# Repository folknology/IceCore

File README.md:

# IceCore
IceCore Ice40 HX based modular developement core 

**Top View**

**Bottom View**

**Features**
* Ice40 HX4K - 4K Luts (8K for Yosys), 80/(128)Kbits BRAM, 2 PLLs, NVCM
* 16Mbit SDRAM 16 bits wide (143Mhz)
* 4Mbit Flash QSPI/SPI (100Mhz)
* 56 General purpose IOs, SPI, Uart, I2C/Can
* Stm32F730 200Mhz, 256KB Ram, 64KB Flash
* Triple 2.5MSPS ADCs (interleaved to 7.2MSPS)
* Dedicated Programming and debug USB 2.0FS
* Uart/Application specific USB2.0FS
* Digital video connector
* SDCard connector
* 4 Coloured Status LEDs
* 4 Coloured User LEDs
* 2 User buttons, 1 Mode/Boot buttoni

[Get it from Tindie as part of BlackIce Mx](https://www.tindie.com/products/Folknology/blackice-mx/)

Core modules can be combined with different carrier boards for example [BlackIce Mx](https://github.com/folknology/BlackIceMx)

Supports the [BlackEdge connectivity](https://github.com/folknology/BlackEdge) carriers

Some further [background information](https://forum.mystorm.uk/t/new-product-blackice-mx/551/10) can be found on the [myStorm forum](https://forum.mystorm.uk)

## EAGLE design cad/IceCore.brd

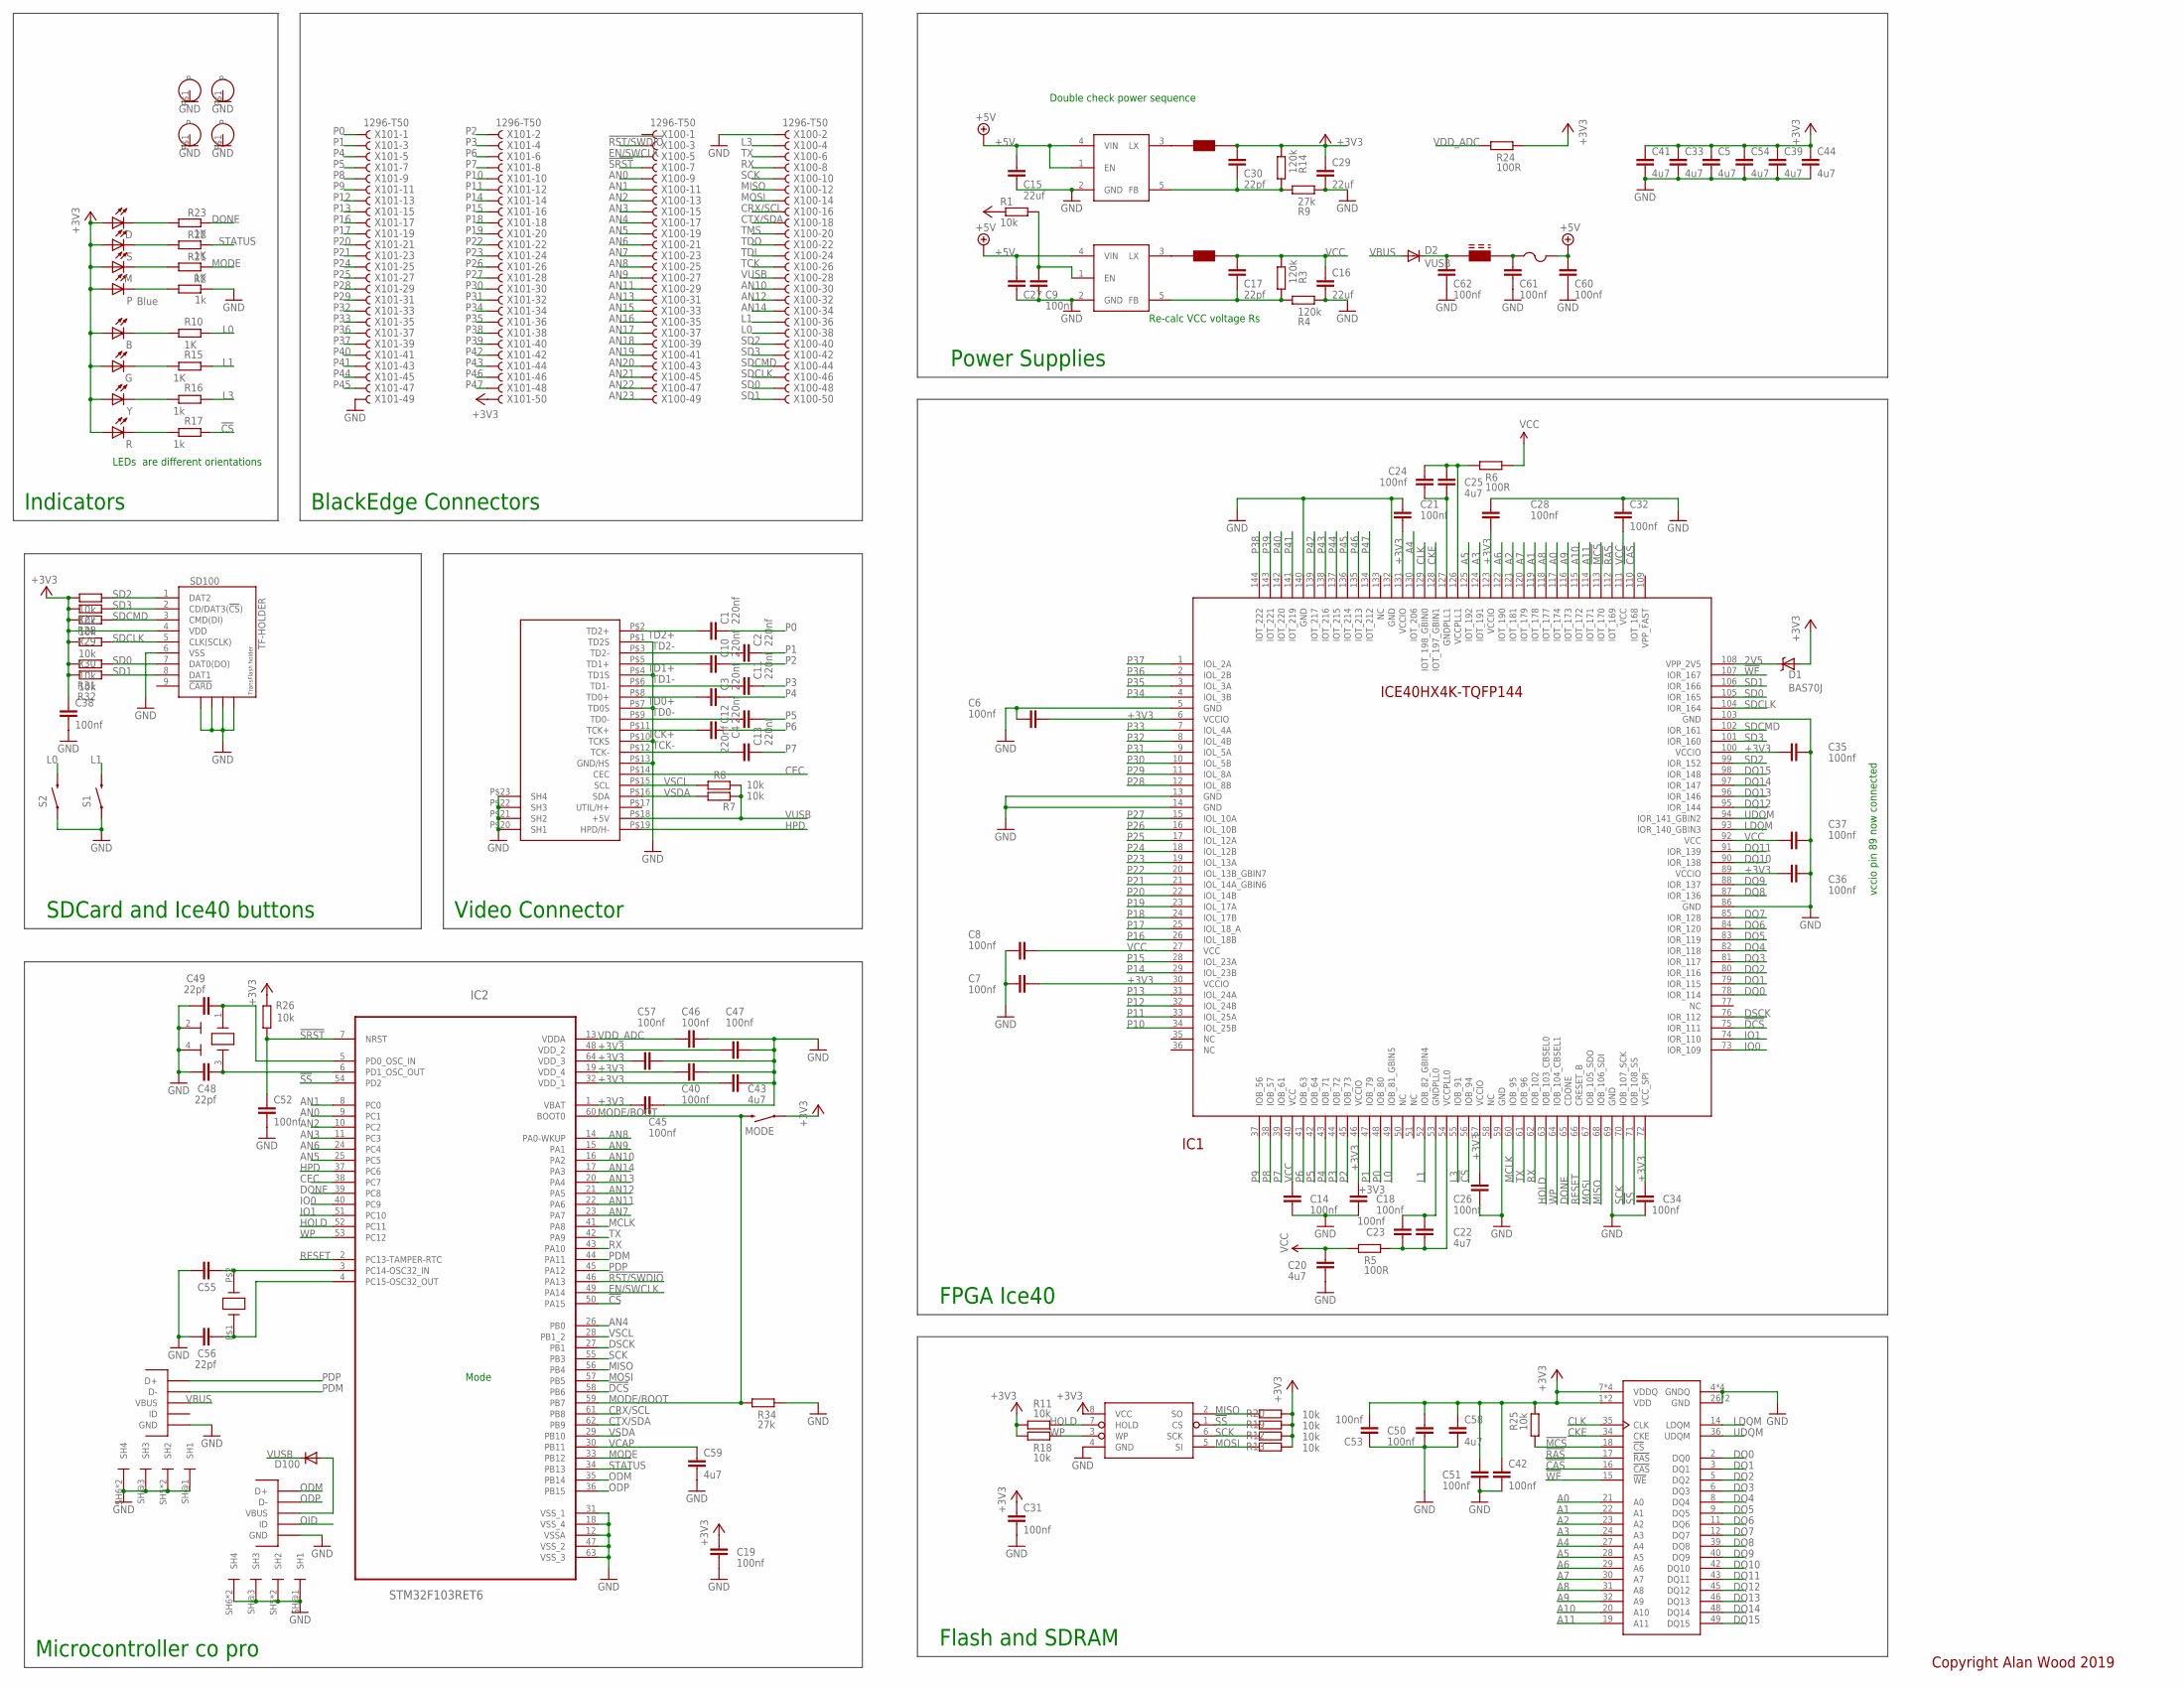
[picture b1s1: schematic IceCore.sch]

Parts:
B: LEDCHIPLED_0603; CHIPLED_0603
C1, C2, C3, C4, C10, C11, C12, C13: 220nf; C0402
C5, C20, C22, C25, C33, C39, C41, C43, C44, C54, C58, C59: 4u7; C0402
C6, C7, C8, C9, C14, C18, C19, C21, C23, C24, C26, C28, C31, C32, C34, C35, C36, C37, C38, C40, C42, C45, C46, C47, C50, C51, C52, C53, C57, C60, C61, C62: 100nf; C0402
C15, C16, C27, C29: 22uf; C0603
C17, C30, C48, C49, C55, C56: 22pf; C0402
COM: FCI-MICROUSB-B-PEG; MICROUSB-B-PEG
D: LEDCHIPLED_0603; CHIPLED_0603
D1: BAS70J; SOD-323
D2, D100: DIODE-SOD123; SOD123
F1: PTCFUSE-1206; R1206
FB1: FERRITE_BEAD; 0603
G: LEDCHIPLED_0603; CHIPLED_0603
IC1: ICE40HX4K_TQFP144; TQFP144
IC2: STM32F103RET6; QFP50P1200X1200X160-64N
IC3: SDRAM; TSOP-2-50
M: LEDCHIPLED_0603; CHIPLED_0603
MODE: SWITCH-MOMENTARY-2SMD-1101NE; TACTILE-SWITCH-1101NE
P: Blue; CHIPLED_0603
R: LEDCHIPLED_0603; CHIPLED_0603
R1, R7, R8, R11, R12, R13, R18, R19, R20, R25, R26, R27, R28, R29, R30, R31, R32: 10k; R0402
R2, R16, R17: 1k; R0402
R3, R4, R14: 120k; R0402
R5, R6, R24: 100R; R0402
R9, R34: 27k; R0402
R10, R15, R21, R22, R23: 1K; R0402
S: LEDCHIPLED_0603; CHIPLED_0603
S1, S2: SWITCH-MOMENTARY-2SMD-1101NE; TACTILE-SWITCH-1101NE
SD100: TF-HOLDER; TF-PULL
U$1, U$2, U$12, U$13: HOLE-2.5MM; 2.5MM-HOLE
U$3, U$6: AP3429/A; TSOP-5/SOT23-5
U$4, U$7: NRS4018; NRC4018
U$5: HD10-001_HDMIMINI-HDMI; MINI-HDMI
U$8: AT25SDF041A; SOIC-8-NARROW
U$10: FCI-MICROUSB-B-PEG; MICROUSB-B-PEG
U$11: FC-135; FC135
X100, X101: 1296-T50; 1296-50
Y: LEDCHIPLED_0603; CHIPLED_0603
Y1: 12MZ; CRYSTAL-3.2X2.5

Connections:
2V5: D1.C, IC1.108 (VPP_2V5)
!CAS: IC1.110 (IOT_168), IC3.16 (!CAS)
!CS: IC1.56 (IOB_94), IC2.50 (PA15), R17.2
!DCS: IC1.75 (IOR_111), IC2.58 (PB6)
!MCS: IC1.113 (IOT_170), IC3.18 (!CS), R25.1
!RAS: IC1.112 (IOT_169), IC3.17 (!RAS)
!RST/SWDIO: IC2.46 (PA13), X100.3
!SRST: C52.1, IC2.7 (NRST), R26.1, X100.7
!SS: IC1.71 (IOB_108_SS), IC2.54 (PD2), R19.2, U$8.1 (CS)
!WE: IC1.107 (IOR_167), IC3.15 (!WE)
+3V3: B.A, C5.1, C6.1, C7.2, C18.1, C19.1, C21.1, C26.1, C28.2, C29.1, C30.2, C31.1, C33.1, C34.1, C35.1, C36.1, C38.1, C39.1, C40.2, C41.1, C42.1, C43.2, C44.1, C45.2, C47.2, C50.1, C51.1, C53.2, C54.1, C57.2, C58.1, D.A, D1.A, G.A, IC1.6 (VCCIO), IC1.30 (VCCIO), IC1.46 (VCCIO), IC1.57 (VCCIO), IC1.72 (VCC_SPI), IC1.89 (VCCIO), IC1.100 (VCCIO), IC1.123 (VCCIO), IC1.131 (VCCIO), IC2.1 (VBAT), IC2.19 (VDD_4), IC2.32 (VDD_1), IC2.48 (VDD_2), IC2.64 (VDD_3), IC3.1 (VDD), IC3.7 (VDDQ), IC3.13 (VDDQ), IC3.25 (VDD), IC3.38 (VDDQ), IC3.44 (VDDQ), M.A, MODE.1, P.A, R.A, R1.1, R11.1, R12.1, R13.1, R14.2, R18.1, R19.1, R20.1, R24.1, R25.2, R26.2, R27.2, R28.2, R29.2, R30.2, R31.2, R32.2, S.A, SD100.4 (VDD), U$7.P$2, U$8.8 (VCC), X101.50, Y.A
+5V: C15.2, C27.2, C60.2, F1.2, U$3.4 (VIN), U$6.1 (EN), U$6.4 (VIN)
A0: IC1.117 (IOT_174), IC3.21 (A0)
A1: IC1.119 (IOT_178), IC3.22 (A1)
A2: IC1.121 (IOT_181), IC3.23 (A2)
A3: IC1.124 (IOT_191), IC3.24 (A3)
A4: IC1.130 (IOT_206), IC3.27 (A4)
A5: IC1.125 (IOT_192), IC3.28 (A5)
A6: IC1.122 (IOT_190), IC3.29 (A6)
A7: IC1.120 (IOT_179), IC3.30 (A7)
A8: IC1.118 (IOT_177), IC3.31 (A8)
A9: IC1.116 (IOT_173), IC3.32 (A9)
A10: IC1.115 (IOT_172), IC3.20 (A10)
A11: IC1.114 (IOT_171), IC3.19 (A11)
AN0: IC2.9 (PC1), X100.9
AN1: IC2.8 (PC0), X100.11
AN2: IC2.10 (PC2), X100.13
AN3: IC2.11 (PC3), X100.15
AN4: IC2.26 (PB0), X100.17
AN5: IC2.25 (PC5), X100.19
AN6: IC2.24 (PC4), X100.21
AN7: IC2.23 (PA7), X100.23
AN8: IC2.14 (PA0-WKUP), X100.25
AN9: IC2.15 (PA1), X100.27
AN10: IC2.16 (PA2), X100.30
AN11: IC2.22 (PA6), X100.29
AN12: IC2.21 (PA5), X100.32
AN13: IC2.20 (PA4), X100.31
AN14: IC2.17 (PA3), X100.34
AN15: X100.33
AN16: X100.35
AN17: X100.37
AN18: X100.39
AN19: X100.41
AN20: X100.43
AN21: X100.45
AN22: X100.47
AN23: X100.49
CEC: IC2.38 (PC7), U$5.P$14 (CEC)
CKE: IC1.128 (IOT_197_GBIN1), IC3.34 (CKE)
CLK: IC1.129 (IOT_198_GBIN0), IC3.35 (CLK)
CRX/SCL: IC2.61 (PB8), X100.16
CTX/SDA: IC2.62 (PB9), X100.18
DONE: IC1.65 (CDONE), IC2.39 (PC8), R23.1
DQ0: IC1.78 (IOR_114), IC3.2 (DQ0)
DQ1: IC1.79 (IOR_115), IC3.3 (DQ1)
DQ2: IC1.80 (IOR_116), IC3.5 (DQ2)
DQ3: IC1.81 (IOR_117), IC3.6 (DQ3)
DQ4: IC1.82 (IOR_118), IC3.8 (DQ4)
DQ5: IC1.83 (IOR_119), IC3.9 (DQ5)
DQ6: IC1.84 (IOR_120), IC3.11 (DQ6)
DQ7: IC1.85 (IOR_128), IC3.12 (DQ7)
DQ8: IC1.87 (IOR_136), IC3.39 (DQ8)
DQ9: IC1.88 (IOR_137), IC3.40 (DQ9)
DQ10: IC1.90 (IOR_138), IC3.42 (DQ10)
DQ11: IC1.91 (IOR_139), IC3.43 (DQ11)
DQ12: IC1.95 (IOR_144), IC3.45 (DQ12)
DQ13: IC1.96 (IOR_146), IC3.46 (DQ13)
DQ14: IC1.97 (IOR_147), IC3.48 (DQ14)
DQ15: IC1.98 (IOR_148), IC3.49 (DQ15)
DSCK: IC1.76 (IOR_112), IC2.27 (PB1)
EN/SWCLK: IC2.49 (PA14), X100.5
GND: C5.2, C6.2, C7.1, C8.2, C9.1, C14.2, C15.1, C16.2, C18.2, C19.2, C20.2, C21.2, C26.2, C27.1, C28.1, C29.2, C31.2, C32.1, C33.2, C34.2, C35.2, C36.2, C37.2, C38.2, C39.2, C40.1, C41.2, C42.2, C43.1, C44.2, C45.1, C46.1, C47.1, C48.1, C49.1, C50.2, C51.2, C52.2, C53.1, C54.2, C55.1, C56.1, C57.1, C58.2, C59.2, C60.1, C61.1, C62.1, COM.P$5 (GND), COM.SH5 (SH2), COM.SH6 (SH4), COM.SH@1 (SH1), COM.SH@2 (SH2), COM.SH@3 (SH3), COM.SH@4 (SH4), IC1.5 (GND), IC1.13 (GND), IC1.14 (GND), IC1.59 (GND), IC1.69 (GND), IC1.86 (GND), IC1.103 (GND), IC1.132 (GND), IC1.140 (GND), IC2.12 (VSSA), IC2.18 (VSS_4), IC2.31 (VSS_1), IC2.47 (VSS_2), IC2.63 (VSS_3), IC3.4 (GNDQ), IC3.10 (GNDQ), IC3.26 (GND), IC3.41 (GNDQ), IC3.47 (GNDQ), IC3.50 (GND), R2.1, R4.2, R9.2, R34.2, S1.1, S2.1, SD100.6 (VSS), SD100.S1, SD100.S2, SD100.S3, SD100.S4, U$1.P$1, U$2.P$1, U$3.2 (GND), U$5.P$1 (TD2S), U$5.P$4 (TD1S), U$5.P$7 (TD0S), U$5.P$10 (TCKS), U$5.P$13 (GND/HS), U$5.P$20 (SH1), U$5.P$21 (SH2), U$5.P$22 (SH3), U$5.P$23 (SH4), U$6.2 (GND), U$8.4 (GND), U$10.P$5 (GND), U$10.SH5 (SH2), U$10.SH6 (SH4), U$10.SH@1 (SH1), U$10.SH@2 (SH2), U$10.SH@3 (SH3), U$10.SH@4 (SH4), U$12.P$1, U$13.P$1, X100.2, X101.49, Y1.2 (GND), Y1.4 (GND)
HOLD: IC1.63 (IOB_103_CBSEL0), IC2.52 (PC11), R11.2, U$8.7 (HOLD)
HPD: IC2.37 (PC6), U$5.P$19 (HPD/H-)
IO0: IC1.73 (IOR_109), IC2.40 (PC9)
IO1: IC1.74 (IOR_110), IC2.51 (PC10)
L0: IC1.49 (IOB_81_GBIN5), R10.2, S2.2, X100.38
L1: IC1.52 (IOB_82_GBIN4), R15.2, S1.2, X100.36
L3: IC1.55 (IOB_91), R16.2, X100.4
LDQM: IC1.93 (IOR_140_GBIN3), IC3.14 (LDQM)
MCLK: IC1.60 (IOB_95), IC2.41 (PA8)
MISO: IC1.68 (IOB_106_SDI), IC2.56 (PB4), R20.2, U$8.2 (SO), X100.12
MODE: IC2.33 (PB12), R21.1
MODE/BOOT: IC2.59 (PB7), IC2.60 (BOOT0), MODE.2, R34.1
MOSI: IC1.67 (IOB_105_SDO), IC2.57 (PB5), R13.2, U$8.5 (SI), X100.14
unnamed: P.C, R2.2
unnamed: R22.2, S.C
unnamed: C24.2, C25.2, IC1.126 (VCCPLL1), R6.2
unnamed: M.C, R21.2
unnamed: C56.2, IC2.4 (PC15-OSC32_OUT), U$11.P$1 (X1)
unnamed: C22.1, C23.2, IC1.53 (GNDPLL0)
unnamed: C48.2, IC2.6 (PD1_OSC_OUT), Y1.3 (X2)
unnamed: C9.2, R1.2, U$3.1 (EN)
unnamed: B.C, R10.1
unnamed: C55.2, IC2.3 (PC14-OSC32_IN), U$11.P$2 (X2)
unnamed: G.C, R15.1
unnamed: R16.1, Y.C
unnamed: COM.P$1 (VBUS), D100.A
unnamed: C24.1, C25.1, IC1.127 (GNDPLL1)
unnamed: R.C, R17.1
unnamed: C61.2, F1.1, FB1.2
unnamed: C22.2, C23.1, IC1.54 (VCCPLL0), R5.1
unnamed: C49.2, IC2.5 (PD0_OSC_IN), Y1.1 (X1)
unnamed: D.C, R23.2
unnamed: U$3.3 (LX), U$4.P$1
unnamed: C17.1, R3.1, R4.1, U$3.5 (FB)
unnamed: C30.1, R9.1, R14.1, U$6.5 (FB)
unnamed: U$6.3 (LX), U$7.P$1
ODM: COM.P$3 (D+), IC2.35 (PB14)
ODP: COM.P$2 (D-), IC2.36 (PB15)
OID: COM.P$4 (ID)
P0: C1.1, IC1.48 (IOB_80), X101.1
P1: C2.1, IC1.47 (IOB_79), X101.3
P2: C10.1, IC1.45 (IOB_73), X101.2
P3: C11.1, IC1.44 (IOB_72), X101.4
P4: C3.1, IC1.43 (IOB_71), X101.5
P5: C4.2, IC1.42 (IOB_64), X101.7
P6: C12.1, IC1.41 (IOB_63), X101.6
P7: C13.1, IC1.39 (IOB_61), X101.8
P8: IC1.38 (IOB_57), X101.9
P9: IC1.37 (IOB_56), X101.11
P10: IC1.34 (IOL_25B), X101.10
P11: IC1.33 (IOL_25A), X101.12
P12: IC1.32 (IOL_24B), X101.13
P13: IC1.31 (IOL_24A), X101.15
P14: IC1.29 (IOL_23B), X101.14
P15: IC1.28 (IOL_23A), X101.16
P16: IC1.26 (IOL_18B), X101.17
P17: IC1.25 (IOL_18_A), X101.19
P18: IC1.24 (IOL_17B), X101.18
P19: IC1.23 (IOL_17A), X101.20
P20: IC1.22 (IOL_14B), X101.21
P21: IC1.21 (IOL_14A_GBIN6), X101.23
P22: IC1.20 (IOL_13B_GBIN7), X101.22
P23: IC1.19 (IOL_13A), X101.24
P24: IC1.18 (IOL_12B), X101.25
P25: IC1.17 (IOL_12A), X101.27
P26: IC1.16 (IOL_10B), X101.26
P27: IC1.15 (IOL_10A), X101.28
P28: IC1.12 (IOL_8B), X101.29
P29: IC1.11 (IOL_8A), X101.31
P30: IC1.10 (IOL_5B), X101.30
P31: IC1.9 (IOL_5A), X101.32
P32: IC1.8 (IOL_4B), X101.33
P33: IC1.7 (IOL_4A), X101.35
P34: IC1.4 (IOL_3B), X101.34
P35: IC1.3 (IOL_3A), X101.36
P36: IC1.2 (IOL_2B), X101.37
P37: IC1.1 (IOL_2A), X101.39
P38: IC1.144 (IOT_222), X101.38
P39: IC1.143 (IOT_221), X101.40
P40: IC1.142 (IOT_220), X101.41
P41: IC1.141 (IOT_219), X101.43
P42: IC1.139 (IOT_217), X101.42
P43: IC1.138 (IOT_216), X101.44
P44: IC1.137 (IOT_215), X101.45
P45: IC1.136 (IOT_214), X101.47
P46: IC1.135 (IOT_213), X101.46
P47: IC1.134 (IOT_212), X101.48
PDM: IC2.44 (PA11), U$10.P$2 (D-)
PDP: IC2.45 (PA12), U$10.P$3 (D+)
RESET: IC1.66 (CRESET_B), IC2.2 (PC13-TAMPER-RTC)
RX: IC1.62 (IOB_102), IC2.43 (PA10), X100.8
SCK: IC1.70 (IOB_107_SCK), IC2.55 (PB3), R12.2, U$8.6 (SCK), X100.10
SD0: IC1.105 (IOR_165), R31.1, SD100.7 (DAT0(DO)), X100.48
SD1: IC1.106 (IOR_166), R32.1, SD100.8 (DAT1), X100.50
SD2: IC1.99 (IOR_152), R27.1, SD100.1 (DAT2), X100.40
SD3: IC1.101 (IOR_160), R28.1, SD100.2 (CD/DAT3(!CS!)), X100.42
SDCLK: IC1.104 (IOR_164), R30.1, SD100.5 (CLK(SCLK)), X100.46
SDCMD: IC1.102 (IOR_161), R29.1, SD100.3 (CMD(DI)), X100.44
STATUS: IC2.34 (PB13), R22.1
TCK: X100.26
TCK+: C12.2, U$5.P$11 (TCK+)
TCK-: C13.2, U$5.P$12 (TCK-)
TD0+: C3.2, U$5.P$8 (TD0+)
TD0-: C4.1, U$5.P$9 (TD0-)
TD1+: C10.2, U$5.P$5 (TD1+)
TD1-: C11.2, U$5.P$6 (TD1-)
TD2+: C1.2, U$5.P$2 (TD2+)
TD2-: C2.2, U$5.P$3 (TD2-)
TDI: X100.24
TDO: X100.22
TMS: X100.20
TX: IC1.61 (IOB_96), IC2.42 (PA9), X100.6
UDQM: IC1.94 (IOR_141_GBIN2), IC3.36 (UDQM)
VBUS: D2.A, U$10.P$1 (VBUS)
VCAP: C59.1, IC2.30 (PB11)
VCC: C8.1, C14.1, C16.1, C17.2, C20.1, C32.2, C37.1, IC1.27 (VCC), IC1.40 (VCC), IC1.92 (VCC), IC1.111 (VCC), R3.2, R5.2, R6.1, U$4.P$2
VDD_ADC: C46.2, IC2.13 (VDDA), R24.2
VSCL: IC2.28 (PB1_2), R8.2, U$5.P$15 (SCL)
VSDA: IC2.29 (PB10), R7.2, U$5.P$16 (SDA)
VUSB: C62.2, D2.C, D100.C, FB1.1, R7.1, R8.1, U$5.P$18 (+5V), X100.28
WP: IC1.64 (IOB_104_CBSEL1), IC2.53 (PC12), R18.2, U$8.3 (WP)

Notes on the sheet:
BlackEdge Connectors
Video Connector
FPGA Ice40
Flash and SDRAM
Microcontroller co pro
SDCard and Ice40 buttons
vccio pin 89 now connected
Re-calc VCC voltage Rs
Indicators
Power Supplies
Double check power sequence
LEDs are different orientations
Mode
Copyright Alan Wood 2019

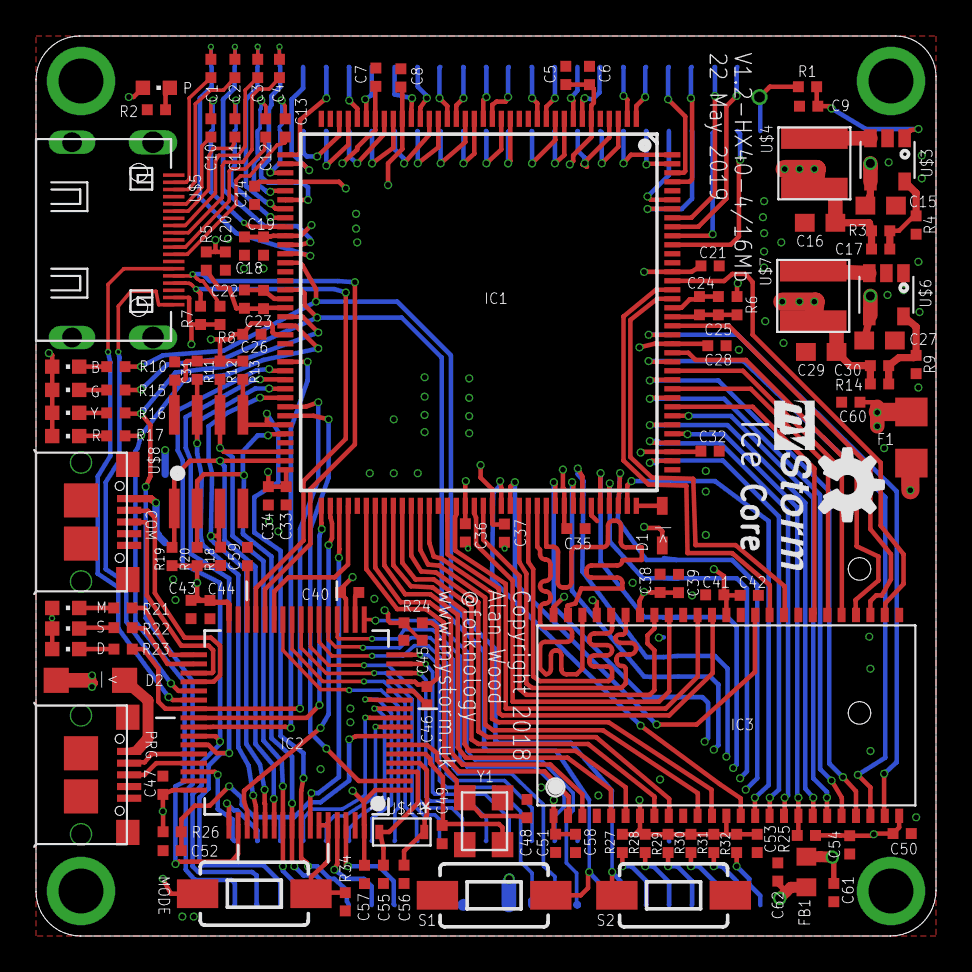
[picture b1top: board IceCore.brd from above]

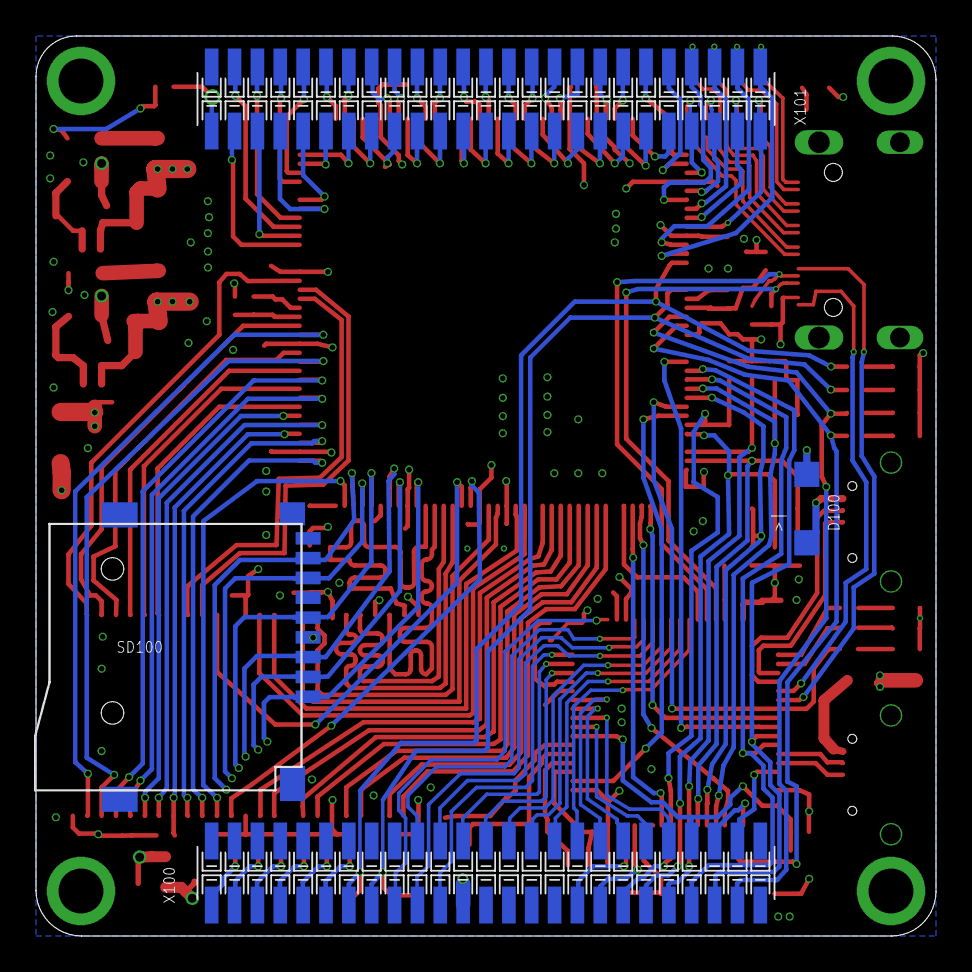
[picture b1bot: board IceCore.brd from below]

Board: 4 copper layers, 50.0 x 50.0 mm, 131 parts (4 on the bottom side), 180 nets.

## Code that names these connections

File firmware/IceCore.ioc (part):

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Mcu.Name=STM32F730R8Tx
Mcu.Package=LQFP64
Mcu.UserName=STM32F730R8Tx
PA0-WKUP.Signal=ADCx_IN0
PA1.Signal=ADCx_IN1
PA10.Mode=Asynchronous
PA10.Signal=USART1_RX
PA11.Mode=Device_Only
PA11.Signal=USB_OTG_FS_DM
PA12.Mode=Device_Only
PA12.Signal=USB_OTG_FS_DP
PA13.Mode=Serial_Wire
PA13.Signal=SYS_JTMS-SWDIO
PA14.Mode=Serial_Wire
PA14.Signal=SYS_JTCK-SWCLK
PA15.Mode=NSS_Signal_Hard_Input
PA15.Signal=SPI3_NSS
PA2.Signal=ADCx_IN2
PA3.Signal=ADCx_IN3
PA4.Signal=ADCx_IN4
PA5.Signal=ADCx_IN5
PA6.Signal=ADCx_IN6
PA7.Signal=ADCx_IN7
PA8.Mode=Clock-out-1
PA8.Signal=RCC_MCO_1
PA9.Mode=Asynchronous
PA9.Signal=USART1_TX
PB0.Signal=ADCx_IN8
PB1.Signal=ADCx_IN9
PB10.Mode=I2C
PB10.Signal=I2C2_SCL
PB11.Mode=I2C
PB11.Signal=I2C2_SDA
PB12.GPIOParameters=GPIO_Label
PB12.GPIO_Label=MODE_LED
PB12.Signal=GPIO_Output
PB13.GPIOParameters=GPIO_Label
PB13.GPIO_Label=STATUS_LED
PB13.Signal=GPIO_Output
PB2.Mode=Single Bank 1 2IOs
PB2.Signal=QUADSPI_CLK
PB3.Mode=Full_Duplex_Slave
PB3.Signal=SPI3_SCK
PB4.Mode=Full_Duplex_Slave
PB4.Signal=SPI3_MISO
PB5.Mode=Full_Duplex_Slave
PB5.Signal=SPI3_MOSI
PB6.Mode=Single Bank 1 2IOs
PB6.Signal=QUADSPI_BK1_NCS
PB7.GPIOParameters=GPIO_Label
PB7.GPIO_Label=MODE_BOOT
PB7.Signal=GPIO_Input
PB8.Mode=I2C
PB8.Signal=I2C1_SCL
PB9.Mode=I2C
PB9.Signal=I2C1_SDA
PC0.Signal=ADCx_IN10
PC1.Signal=ADCx_IN11
PC10.Mode=Single Bank 1 2IOs
PC10.Signal=QUADSPI_BK1_IO1
PC11.GPIOParameters=GPIO_Label,GPIO_ModeDefaultOutputPP
PC11.GPIO_Label=ICE40_HOLD
PC11.GPIO_ModeDefaultOutputPP=GPIO_MODE_OUTPUT_OD
PC11.Signal=GPIO_Output
PC12.GPIOParameters=GPIO_Label,GPIO_ModeDefaultOutputPP
PC12.GPIO_Label=ICE40_WP
PC12.GPIO_ModeDefaultOutputPP=GPIO_MODE_OUTPUT_OD
PC12.Signal=GPIO_Output
PC13.GPIOParameters=GPIO_Label
PC13.GPIO_Label=ICE40_CRST
PC13.Signal=GPIO_Output
PC14-OSC32_IN.Mode=LSE-External-Oscillator
PC14-OSC32_IN.Signal=RCC_OSC32_IN
PC15-OSC32_OUT.Mode=LSE-External-Oscillator
PC15-OSC32_OUT.Signal=RCC_OSC32_OUT
PC2.Signal=ADCx_IN12
PC3.Signal=ADCx_IN13
PC4.Signal=ADCx_IN14
PC6.GPIOParameters=GPIO_PuPd,GPIO_Label
PC6.GPIO_Label=HDMI_HPD
PC6.GPIO_PuPd=GPIO_PULLDOWN
PC6.Signal=GPIO_Input
PC7.GPIOParameters=GPIO_Label
PC7.GPIO_Label=HDMI_CEC
PC7.Signal=GPIO_Output
PC8.GPIOParameters=GPIO_Label,GPIO_ModeDefaultEXTI
PC8.GPIO_Label=ICE40_CDONE
PC8.GPIO_ModeDefaultEXTI=GPIO_MODE_IT_RISING_FALLING
PC8.Signal=GPXTI8
PC9.Mode=Single Bank 1 2IOs
PC9.Signal=QUADSPI_BK1_IO0
PD2.GPIOParameters=GPIO_Label,GPIO_ModeDefaultOutputPP
PD2.GPIO_Label=ICE40_SPI_CS
PD2.GPIO_ModeDefaultOutputPP=GPIO_MODE_OUTPUT_OD
PD2.Signal=GPIO_Output
PH0-OSC_IN.Mode=HSE-External-Oscillator
PH0-OSC_IN.Signal=RCC_OSC_IN
PH1-OSC_OUT.Mode=HSE-External-Oscillator
PH1-OSC_OUT.Signal=RCC_OSC_OUT
RCC.HSE_VALUE=25000000
RCC.SYSCLKFreq_VALUE=216000000
RCC.SYSCLKSource=RCC_SYSCLKSOURCE_PLLCLK
board=custom

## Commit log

2019-05-18 Initial commit of IceCore cad
2019-05-18 Cropped proto image
2019-05-18 Cropped layout image
2019-05-18 Added solderpad hardware license
2019-05-18 Fixed typo in readme
2019-05-18 Added Schematic preview image
2019-05-18 Added Schematic preview image to readme
2019-05-18 Updated IceCore images
2019-05-18 Added IceCore Bottom of board shot
2019-05-18 Updated IceCore date information in CAD
2019-07-02 Added first BIMx Verilog example (trail)
2019-07-02 Added comprehensive PCF file for reference
2019-07-02 Added blink example
2019-07-02 Changed blink to red led rather than blue (also button!)
2019-07-03 Fixed led index, doh!
2019-07-03 Added stty -F /dev/ttyACM0 raw to make file upload target
2019-07-03 Updated IceCore JPEG to manufactured board
2019-07-03 Updated IceCore bottom JPEG to manufactured board
2019-07-03 Updated IceCore board
2019-07-03 Updated Readme - ref BlackEdge repo
2019-07-03 Added initial myStorm iceboot firmware
2019-07-03 Fix Yosys misspelling.
2019-07-03 Renamed clk to rclk (SDRAM clock) and stop it conflicting with 25mhz clk
2019-07-04 Added BSD License to iceboot
2019-07-04 Updated BSD License in iceboot
2019-07-04 Added missing Drivers for the firmware
2019-07-05 Re wrote BlackIce PCF file
2019-07-05 Updated BlackIceMx pcf file
2019-07-06 Corrected SRAM clock name to rclk in pcf file
2019-07-10 Added linbk to tindie
2019-07-11 Renamed Cuubemx IceCore file
2019-07-21 Initial refactor, including Uart/Usb, but not yet working and lots to clear up
2019-07-28 Added working mystorm files
2019-07-28 Removed olde iceboot
2019-07-28 Added missing driver files
2019-07-29 Added missing source files from Src into mystorm dir
2019-07-29 Added back the Host ->USB->Uart->Ice40 now that I have tunred the auto echo off!!
2019-07-29 Removed another silly CubeMx generated template file
2019-07-29 Added line echo example borrowed from Zipcpu
2019-07-30 Wrapped Flash access in SPI Enable/Disable to make suure writes don not occur without GPIOs interfering
2019-07-30 Added simple error counter
2019-07-30 Added ERR chars
2019-07-30 Errors by buutton only now
2019-07-30 Error cleared by button
2019-07-30 updated binary with error code
2019-07-30 Added @lawrie fix to force CS high on Flashboot
2019-07-30 Changed flashboot default to Flash1
2019-07-30 Changed flashboot default to Flash1 binary
2019-08-02 Changed Interrupt priorities addeds flash code (not yet working), changed spi Enable/Disable
2019-08-03 Improved but stillnot yet working flash code
2019-08-03 Fixed stream return value so uar dma does not kick in
2019-08-03 Ok fixed bug where data was sent more than once (bur re-use)
2019-08-03 Removed silly Ice40 reset code
2019-08-03 The flash code seems good, however it is still not booting from flash..
2019-08-04 Fixed nbytes issue
2019-08-04 Flash programing via the mode switch now works
2019-08-08 Removed more pesky template files from the Drivers/src
2019-08-09 makefile: use HAL objects directly rather than via the drivers static library
    The static library is not really needed. Its only upside is that it allows
    for unused HAL source files to be dropped from the resulting binary. But
    ideally any unused HAL files should just be removed from sources.
    Having the shared library could mask other issues, see:
    https://forum.mystorm.uk/t/building-icecore-firmware/613/16
2019-08-09 remove stray templates that break build
    These are files created by STM32CubeMx but that should not
    be included in the build.
2019-08-09 Added Class to manage leds and state
2019-08-09 Oops got leds mixed up and mode status, fixed now
2019-08-09 Changed led status naming (negated-active low) to better indicate use
2019-09-11 Refactored code, fixed warnings, tamed status led and much more..
2019-09-16 Added mystorm.raw
2021-01-23 Ported pinout to blackicemx (icoboard) to determine pin names in pcf via uart

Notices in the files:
cad/IceCore.brd:
Copyright 2018
parts and their libraries:
SparkFun-Electromechanical: Licensing: Creative Commons ShareAlike 4.0 International - https://creativecommons.org/licenses/by-sa/4.0
